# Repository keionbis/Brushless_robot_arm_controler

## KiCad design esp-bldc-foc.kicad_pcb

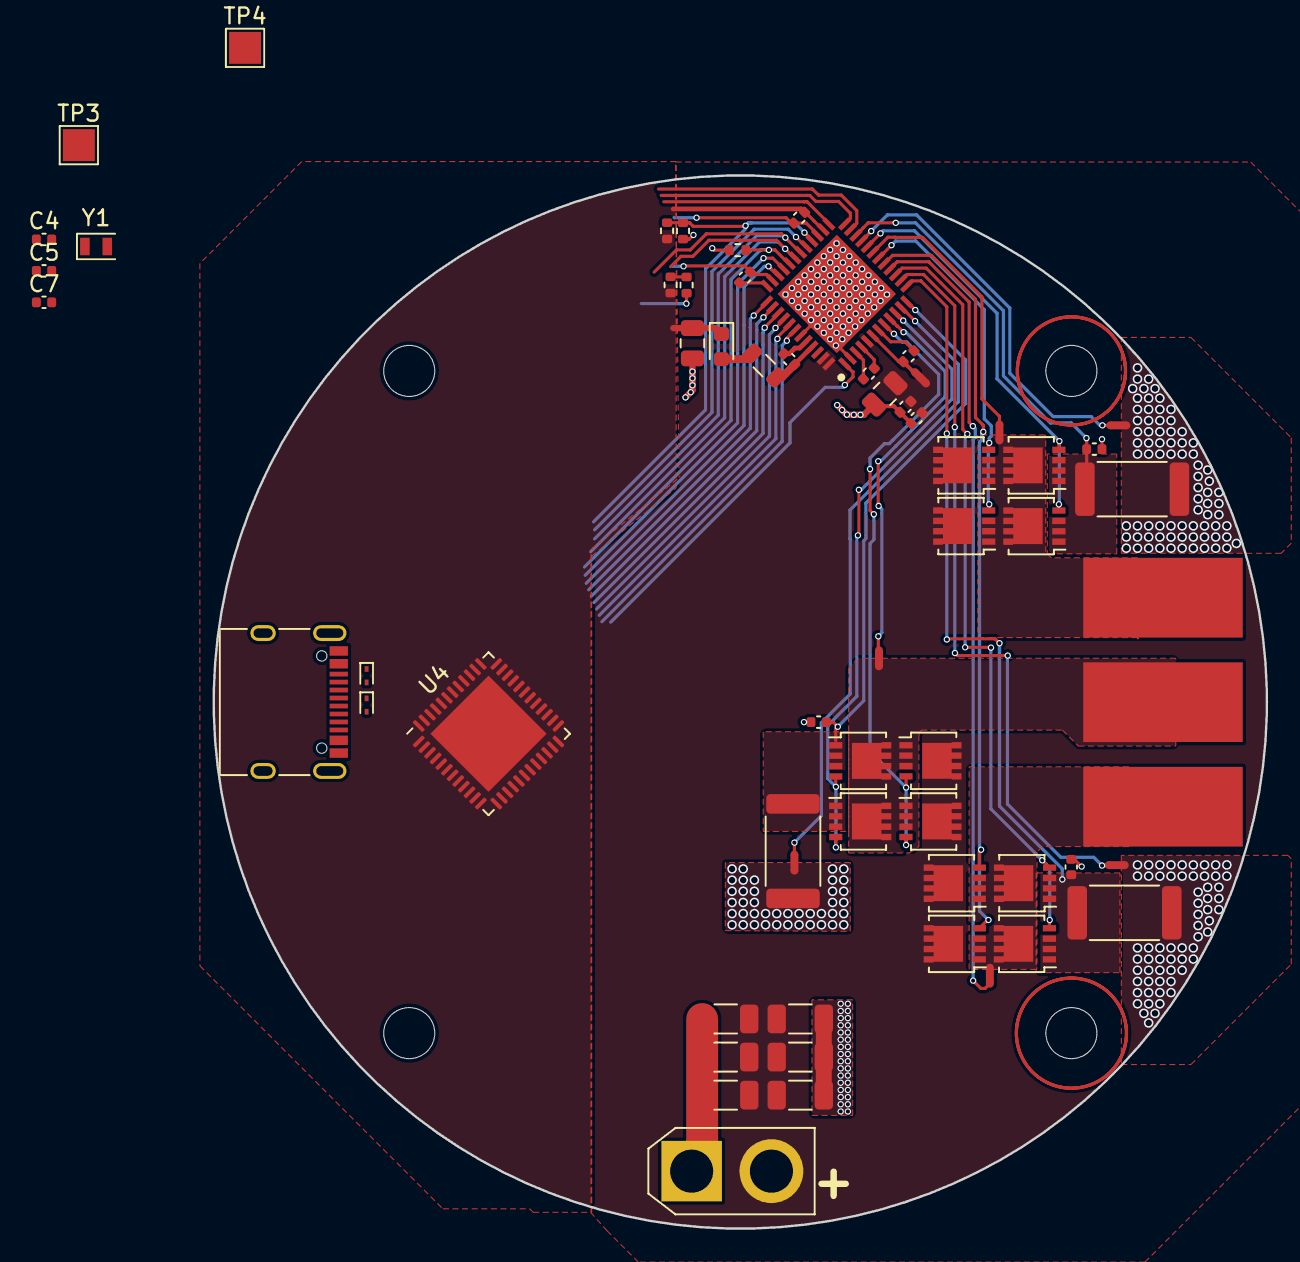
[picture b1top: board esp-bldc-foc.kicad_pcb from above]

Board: 2 copper layers, 66.0 x 66.0 mm, 66 parts (0 on the bottom side), 50 nets.

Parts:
C1: 4.7uF; C_0805_2012Metric
C4, C7: 10pF; C_0402_1005Metric
C5, C11, C16, C17: 0.1uF; C_0402_1005Metric
C8, C14: 1uF; C_0402_1005Metric
C13: 0.047uF; C_0402_1005Metric
C15: 2.2uF; C_0402_1005Metric
C21, C22, C23: 1000pF; C_0402_1005Metric
C24: 22uF; C_0805_2012Metric
C28, C29, C30, C31, C32, C33: 100uF; C_1206_3216Metric
D2, D3: SZESD9B5.0ST5G; D_SOD-923
D4: D; D_0603_1608Metric
H1, H2, H3, H4: MountingHole; MountingHole_3.2mm_M3
IC2: DRV8323RHRGZR; QFN50P700X700X100-49N-D
J1: USB_C_Receptacle_USB2.0; USB_C_Receptacle_XKB_U262-16XN-4BVC11
J6: Conn_01x02_Female; AMASS_XT30U-F_1x02_P5.0mm_Vertical
J7: A; SolderWirePad_1x01_SMD_5x10mm
J8: B; SolderWirePad_1x01_SMD_5x10mm
J9: C; SolderWirePad_1x01_SMD_5x10mm
L1: 15uH; L_0805_2012Metric
NT1, NT2, NT3, NT4, NT5, NT6, NT7: NetTie_2; NetTie-2_SMD_Pad0.5mm
Q1, Q2, Q3, Q4, Q5, Q6, Q7, Q8, Q9, Q10, Q11, Q12: BUK7M9R9-60EX; LFPAK33
R8, R19, R22: 0.002R; R_2512_6332Metric
R15, R16: 75K; R_0402_1005Metric
R20: 47K; R_0402_1005Metric
R24: 10K; R_0402_1005Metric
R25: 330; R_0402_1005Metric
TP3, TP4: TestPoint; TestPoint_Pad_2.0x2.0mm
U4: ATSAMD21G18A-M; QFN-48-1EP_7x7mm_P0.5mm_EP5.15x5.15mm
Y1: 32.7k; Crystal_SMD_2012-2Pin_2.0x1.2mm

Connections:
+3.3V: C5.1, C17.1, C24.1, D4.1 (K), IC2.26 (VREF), R15.1, R24.1, U4.6 (VDDANA), U4.17 (VDDIO), U4.36 (VDDIO), U4.44 (VDDIN)
+5V: J1.A4 (VBUS), J1.A9 (VBUS), J1.B4 (VBUS), J1.B9 (VBUS)
/MCU/D_N: D2.2 (A2), J1.A7 (D-), J1.B7 (D-), U4.33 (PA24)
/MCU/D_P: D3.1 (A1), J1.A6 (D+), J1.B6 (D+), U4.34 (PA25)
/MCU/IO11: IC2.28 (NFAULT), R24.2, R25.1, U4.16 (PA11)
/MCU/IO12: IC2.33 (ENABLE), U4.21 (PA12)
/MCU/IO13: IC2.30 (IDRIVE), U4.22 (PA13)
/MCU/IO14: IC2.29 (MODE), U4.23 (PA14)
/MCU/IO15: IC2.32 (GAIN), R20.1, U4.24 (PA15)
/MCU/IO16: IC2.34 (CAL), U4.25 (PA16)
/MCU/IO17: IC2.31 (VDS), R15.2, R16.1, U4.26 (PA17)
/MCU/IO18: IC2.37 (INHA), U4.27 (PA18)
/MCU/IO19: IC2.38 (INLA), U4.28 (PA19)
/MCU/IO20: IC2.39 (INHB), U4.29 (PA20)
/MCU/IO21: IC2.40 (INLB), U4.30 (PA21)
/MCU/IO22: IC2.41 (INHC), U4.31 (PA22)
/MCU/IO23: IC2.42 (INLC), U4.32 (PA23)
/Power_stage/A: J7.1, NT4.2, Q5.1 (S), Q5.2 (S), Q5.3 (S), Q6.5 (D), Q7.1 (S), Q7.2 (S), Q7.3 (S), Q8.5 (D)
/Power_stage/B: J8.1, NT2.2, Q1.1 (S), Q1.2 (S), Q1.3 (S), Q2.5 (D), Q3.1 (S), Q3.2 (S), Q3.3 (S), Q4.5 (D)
/Power_stage/C: J9.1, NT6.2, Q9.1 (S), Q9.2 (S), Q9.3 (S), Q10.5 (D), Q11.1 (S), Q11.2 (S), Q11.3 (S), Q12.5 (D)
/Power_stage/GHA: IC2.8 (GHA), Q5.4 (G), Q7.4 (G)
/Power_stage/GHB: IC2.17 (GHB), Q1.4 (G), Q3.4 (G)
/Power_stage/GHC: IC2.18 (GHC), Q9.4 (G), Q11.4 (G)
/Power_stage/GLA: IC2.10 (GLA), Q6.4 (G), Q8.4 (G)
/Power_stage/GLB: IC2.15 (GLB), Q2.4 (G), Q4.4 (G)
/Power_stage/GLC: IC2.20 (GLC), Q10.4 (G), Q12.4 (G)
/Power_stage/SHA: IC2.9 (SHA), NT4.1
/Power_stage/SHB: IC2.16 (SHB), NT2.1
/Power_stage/SHC: IC2.19 (SHC), NT6.1
/Power_stage/SN1: C22.1, IC2.12 (SNA), Q6.1 (S), Q6.2 (S), Q6.3 (S), Q8.1 (S), Q8.2 (S), Q8.3 (S), R19.1
/Power_stage/SN2: C21.1, IC2.13 (SNB), Q2.1 (S), Q2.2 (S), Q2.3 (S), Q4.1 (S), Q4.2 (S), Q4.3 (S), R8.1
/Power_stage/SN3: C23.1, IC2.22 (SNC), Q10.1 (S), Q10.2 (S), Q10.3 (S), Q12.1 (S), Q12.2 (S), Q12.3 (S), R22.1
/Power_stage/SP1: IC2.11 (SPA), NT5.1
/Power_stage/SP2: IC2.14 (SPB), NT3.1
/Power_stage/SP3: IC2.21 (SPC), NT7.1
/motor_controller/VDRAIN: C14.1, IC2.6 (VM), NT1.1
GND: C1.2, C11.2, C15.2, C21.2, C22.2, C23.2, C24.2, C28.2, C29.2, C30.2, C31.2, C32.2, C33.2, IC2.2 (PGND), IC2.43 (BGND), IC2.49 (THERMAL_PAD), J6.1, NT3.2, NT5.2, NT7.2, R8.2, R16.2, R19.2, R20.2, R22.2, R25.2
GNDD: C4.2, C5.2, C7.2, C8.2, C17.2, D2.1 (A1), D3.2 (A2), IC2.27 (DGND), IC2.35 (AGND), J1.A1 (GND), J1.A12 (GND), J1.B1 (GND), J1.B12 (GND), J1.S1 (SHIELD), U4.5 (GNDANA), U4.18 (GND), U4.35 (GND), U4.42 (GND), U4.49 (EP)
unnamed: D4.2 (A), L1.2
unnamed: C16.2, IC2.44 (CB)
unnamed: C13.2, IC2.4 (CPH)
unnamed: C13.1, IC2.3 (CPL)
unnamed: C8.1, IC2.36 (DVDD)
unnamed: C16.1, IC2.45 (SW), L1.1
unnamed: C14.2, IC2.7 (VDRAIN)
unnamed: C7.1, U4.1 (PA00), Y1.2
unnamed: C4.1, U4.2 (PA01), Y1.1
unnamed: TP3.1, U4.45 (PA30)
unnamed: TP4.1, U4.46 (PA31)
VBUS: C1.1, C11.1, C15.1, C28.1, C29.1, C30.1, C31.1, C32.1, C33.1, IC2.5 (VCP), IC2.47 (VIN), IC2.48 (NSHDN), J6.2, NT1.2, Q1.5 (D), Q3.5 (D), Q5.5 (D), Q7.5 (D), Q9.5 (D), Q11.5 (D)

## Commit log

2022-08-19 start to brushless motor controller, schematic done, most of the routing is done
2022-08-19 finished routing
2022-08-23 Routing done
2022-08-24 Adding more vias and clenup
2022-08-25 cleaned up zones, removed fill under antenna and added vias for vbus connection to the inner layers
2022-08-25 Adding gerber to git ignore
2022-09-01 Using DRV8353 with built in current sense
2022-09-02 Adding step
2022-09-02 cleaning up silk screen
2023-01-18 init routing done
2023-07-02 designed
2023-07-02 sarted samd21 layout
